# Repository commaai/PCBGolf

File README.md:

<div align="center">
<h1>PCBGolf Challenge</h1>
<h3>How small can you make this PCBA?</h3>
<h3>
  <a href="https://comma.ai/leaderboard#pcbgolf_challenge">Leaderboard</a>
  <span> · </span>
  <a href="https://comma.ai/jobs">comma.ai/jobs</a>
  <span> · </span>
  <a href="https://discord.comma.ai">Discord</a>
  <span> · </span>
  <a href="https://x.com/comma_ai">X</a>
</h3>
</div>

## The Board

The schematic is loosely based on [our panda jungle v2](https://www.comma.ai/shop/panda-jungle), a development and debugging board for comma devices and pandas. This version includes:

* 12V DC input with onboard 5V and 3.3V supplies
* Four [OBD-C](https://github.com/commaai/hardware/blob/master/harness/OBD-C.sch.pdf) device ports with individually controlled power and current monitoring
* Four CAN-FD transceivers and ignition simulation circuitry
* A USB hub and USB-C host connection
* A microcontroller and microSD card slot
* A push button and status LEDs

Explore in your browser with KiCanvas: [PCB layout](https://kicanvas.org/?github=https%3A%2F%2Fgithub.com%2Fcommaai%2FPCBGolf%2Fblob%2Fmaster%2Fpcbgolf.kicad_pcb).

Schematics: [Power](https://kicanvas.org/?github=https%3A%2F%2Fgithub.com%2Fcommaai%2FPCBGolf%2Fblob%2Fmaster%2Fpcbgolf.kicad_sch) · [Microcontroller](https://kicanvas.org/?github=https%3A%2F%2Fgithub.com%2Fcommaai%2FPCBGolf%2Fblob%2Fmaster%2Fpcbgolf_2.kicad_sch) · [USB & microSD](https://kicanvas.org/?github=https%3A%2F%2Fgithub.com%2Fcommaai%2FPCBGolf%2Fblob%2Fmaster%2Fpcbgolf_3.kicad_sch) · [CAN](https://kicanvas.org/?github=https%3A%2F%2Fgithub.com%2Fcommaai%2FPCBGolf%2Fblob%2Fmaster%2Fpcbgolf_4.kicad_sch) · [OBD-C ports](https://kicanvas.org/?github=https%3A%2F%2Fgithub.com%2Fcommaai%2FPCBGolf%2Fblob%2Fmaster%2Fpcbgolf_5.kicad_sch)

## The Challenge

Your goal is to make the most compact, efficient PCBA that retains the same interfaces and functionality as the original design. The lowest score wins.

<p align="center">
  <picture>
    <source media="(prefers-color-scheme: dark)" srcset="./assets/score-dark.svg">
    
  </picture>
</p>

### Rules

* The bare PCB(s) must be fully manufacturable by JLCPCB.
* It must be possible to actually assemble the PCBA.
* The assembled product must work and be usable.
* Mating connectors must remain mechanically and electrically compatible.
* Optimizations that require firmware changes are allowed.

### Prize

Lowest score on the [leaderboard](https://comma.ai/leaderboard#pcbgolf_challenge) by **October 12, 2026** wins **$1,000 cash**.

## Submission

Submit a `.zip` file containing your finalized KiCad project and a STEP file of the final assembly [here](https://forms.gle/US88Hg7UR6bBuW3BA).
Competitive scores will be posted on the [leaderboard](https://comma.ai/leaderboard#pcbgolf_challenge) after review. Multiple submissions allowed.

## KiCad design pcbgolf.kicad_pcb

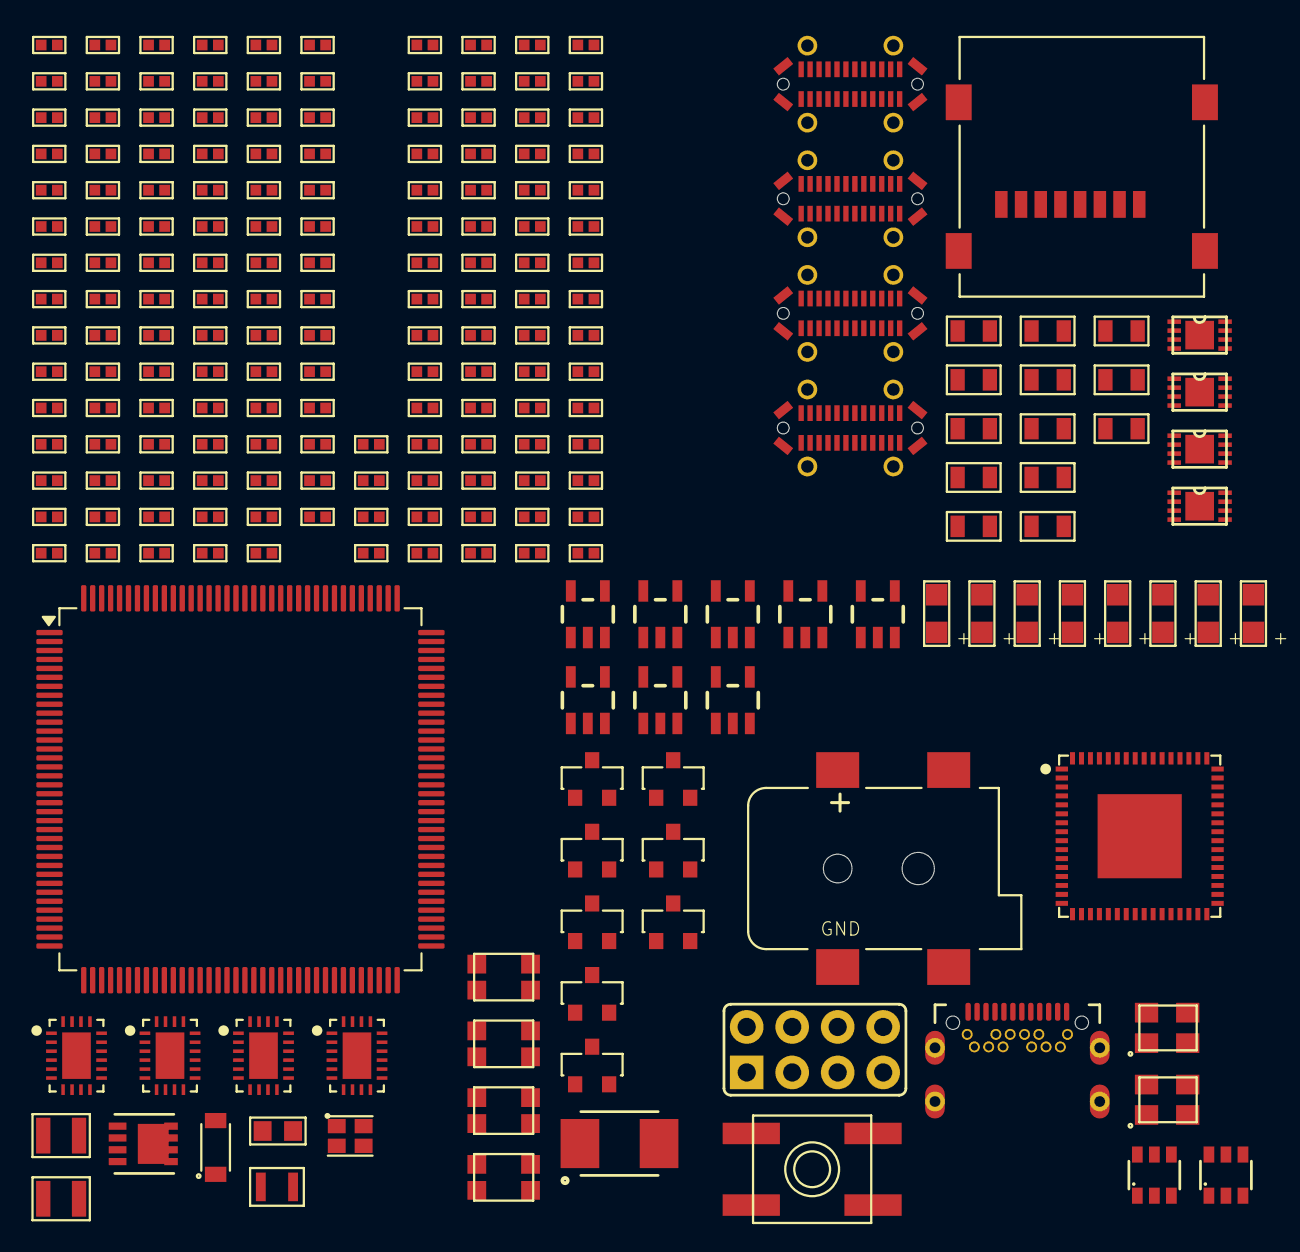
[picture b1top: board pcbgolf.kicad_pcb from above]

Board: 4 copper layers, 225 parts (0 on the bottom side), 183 nets, no tracks yet.

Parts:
C1, C3, C8, C12, C13, C15, C19, C20, C21: 10uF; 0805-C
C2, C4, C5, C7, C9, C11, C16, C18, C22, C23, C24, C26, C27, C30, C31, C35, C36, C38, C39, C40, C41, C42, C43, C44, C45, C46, C47, C48, C49: 100nF; 0402-C
C6, C10: DNP; 0402-C
C14, C17, C28, C32: 12pF; 0402-C
C25: 220pF; 0402-C
C29, C33, C34, C37: 10u; 0402-C
C50, C51, C52, C53: 10u; 0805-C
D1: TVS-BI-DO214AA; DO-214AA(SMB)
D2: DIODEDB2W40100L; SOD-123F
J1: DCBARRELSMT; DCJACK_2MM_SMT
J2: MICRO_SD-0472192001; 0472192001
J3: USB-C-FEMALE; DX07S024XJ1R1100
J4: CAN; 2X04
J5, J6, J7, J8: USB-C-FEMALEGCT; USB-C-FEMALE-VERT-GCT
L1, L2: 3u3; L-1008
L3: L-US-L2; 0603-L
L4: 2u2; 0806
L5, L6, L7, L8: ACT1210D_CHOKE; CHOKE-3.2X2.5
LED1: CREE-RGB-CLMVC
LED2: CAN0; CHIPLED
LED3: CAN1; CHIPLED
LED4: CAN2; CHIPLED
LED5: CAN3; CHIPLED
LED6, LED7, LED8, LED9: CH1_PWR; CHIPLED
LED10, LED11, LED12, LED13, LED14, LED15, LED16, LED17: LED-CC-GREEN-RED-AM23ESG; SOT23-3
Q1: SIS427-VI; PP-1212-8
Q2, Q3, Q4, Q5, Q6, Q7, Q8, Q9: NFET-DUAL-COMMON-SOURCE-QS5K2; SOT23-5
R1, R3, R7, R8, R9, R11, R12, R28, R29, R30, R31, R32, R33, R34, R35, R36, R37, R44, R45, R78, R79, R80, R81, R98, R99, R100, R101, R102, R103, R104, R105, R122, R123, R124, R125: 10k; 0402-R
R2, R21, R23, R90, R92, R94, R96, R114, R116, R118, R120: 1k; 0402-R
R4, R5, R6, R13, R14, R15, R16, R17, R18, R19, R20, R24, R25: 100k; 0402-R
R10: 52k3; 0402-R
R22: 2k7; 0402-R
R26: 1M; 0402-R
R27: 12k; 0402-R
R38, R39, R40, R41, R42, R43: 0R; 0402-R
R46, R47, R48, R49: 60; 0402-R
R62, R63, R64, R65: 330; 0402-R
R66, R67, R68, R69: 28k; 0402-R
R70, R71, R72, R73: 33k; 0402-R
R74, R75, R76, R77: 3k3; 0402-R
R82, R83, R84, R85, R86, R87, R88, R89, R91, R93, R95, R97, R106, R107, R108, R109, R110, R111, R112, R113, R115, R117, R119, R121: 100; 0402-R
SW1: SPST-2-4PIN; EVQ-Q2
U1, U2: AP62300T; SOT23-6
U3: STM32H725ZGTx; LQFP-144_20x20mm_P0.5mm
U4: USB2517; QFN64-9X9
U5, U6, U7, U8: MCP2542FDT-E/MNY; TDFN8_2X3MC_MCH
U13, U14, U15, U16: TPS25942; WQFN20
Y1: 25MHz; XTAL-3.2X2.5
Y2: 24MHz; XTAL-3.2X2.5

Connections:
+3V3: C6.2, C7.1, C8.1, C19.1, C20.1, C23.1, C24.1, C26.1, C27.1, C30.2, C31.2, C37.1, C42.1, C43.1, C44.1, C45.1, J2.4 (VDD), L1.2, L3.1, LED1.U1 (COM+), R4.1, R5.1, R6.1, R11.1, R28.1, R29.1, R30.1, R33.1, R34.1, R35.1, R36.1, R37.1, SW1.B (S), SW1.B' (S1), U3.7 (VDD), U3.8 (VBAT), U3.13 (VDD), U3.16 (VDDSMPS), U3.19 (VDD), U3.32 (VDD), U3.42 (VDD), U3.56 (VDD), U3.71 (VDD), U3.79 (VDD), U3.90 (VDD50USB), U3.91 (VDD33USB), U3.92 (VDD), U3.106 (VDD), U3.119 (VDD), U3.129 (VDD), U3.144 (VDD), U4.5 (VDDA33), U4.10 (VDDA33), U4.13 (CFG_SEL2), U4.24 (VDD33CR), U4.42 (CFG_SEL1), U4.43 (RESET_N), U4.46 (VDD33), U4.52 (VDDA33), U4.57 (VDDA33), U4.64 (VDD33PLL), U5.5 (VIO), U6.5 (VIO), U7.5 (VIO), U8.5 (VIO)
+5V: C1.1, C2.1, C10.2, C11.1, C12.1, C13.1, C38.1, C39.1, C40.1, C41.1, L2.2, R1.1, R10.2, U1.3 (IN), U5.3 (VDD), U6.3 (VDD), U7.3 (VDD), U8.3 (VDD)
+12V: C3.1, C5.1, C46.1, C47.1, C48.1, C49.1, C50.1, C51.1, C52.1, C53.1, D2.1 (C), Q1.1 (S), Q1.2 (S), Q1.3 (S), R7.1, U2.3 (IN), U13.9 (VIN), U13.10 (VIN), U13.11 (VIN), U13.12 (VIN), U13.13 (VIN), U14.9 (VIN), U14.10 (VIN), U14.11 (VIN), U14.12 (VIN), U14.13 (VIN), U15.9 (VIN), U15.10 (VIN), U15.11 (VIN), U15.12 (VIN), U15.13 (VIN), U16.9 (VIN), U16.10 (VIN), U16.11 (VIN), U16.12 (VIN), U16.13 (VIN)
BTN: R12.2, SW1.A, SW1.A' (P1), U3.65 (PE15), U3.135 (BOOT0)
CAN0_EN: U3.134 (PB7), U5.8 (STBY)
CAN0_H: J4.2, J5.A2 (TX1+), J6.A2 (TX1+), J7.A2 (TX1+), J8.A2 (TX1+), L5.4, R46.2
CAN0_L: J4.1, J5.A3 (TX1-), J6.A3 (TX1-), J7.A3 (TX1-), J8.A3 (TX1-), L5.3, R46.1
CAN0_RX: U3.136 (PB8), U5.4 (RXD)
CAN0_TX: U3.137 (PB9), U5.1 (TXD)
CAN1_EN: U3.130 (PB3(JTDO), U6.8 (STBY)
CAN1_H: J4.4, J5.A11 (RX2+), J6.A11 (RX2+), J7.A11 (RX2+), J8.A11 (RX2+), L6.4, R47.2
CAN1_L: J4.3, J5.A10 (RX2-), J6.A10 (RX2-), J7.A10 (RX2-), J8.A10 (RX2-), L6.3, R47.1
CAN1_RX: U3.132 (PB5), U6.4 (RXD)
CAN1_TX: U3.133 (PB6), U6.1 (TXD)
CAN2_EN: U3.121 (PD7), U7.8 (STBY)
CAN2_H: J4.6, J5.B2 (TX2+), J6.B2 (TX2+), J7.B2 (TX2+), J8.B2 (TX2+), L7.4, R48.2
CAN2_L: J4.5, J5.B3 (TX2-), J6.B3 (TX2-), J7.B3 (TX2-), J8.B3 (TX2-), L7.3, R48.1
CAN2_RX: U3.123 (PG10), U7.4 (RXD)
CAN2_TX: U3.122 (PG9), U7.1 (TXD)
CAN3_EN: U3.131 (PB4(NJTRST)), U8.8 (STBY)
CAN3_H: J4.8, J5.B11 (RX1+), J6.B11 (RX1+), J7.B11 (RX1+), J8.B11 (RX1+), L8.4, R49.2
CAN3_L: J4.7, J5.B10 (RX1-), J6.B10 (RX1-), J7.B10 (RX1-), J8.B10 (RX1-), L8.3, R49.1
CAN3_RX: U3.72 (PB12), U8.4 (RXD)
CAN3_TX: U3.73 (PB13), U8.1 (TXD)
CH1_D_N: J5.A7 (D-A), J5.B7 (D-B), U4.1 (USBDN1_DM)
CH1_D_P: J5.A6 (D+A), J5.B6 (D+B), U4.2 (USBDN1_DP)
CH1_IMON: R70.2, U3.47 (PC4), U13.19 (IMON)
CH1_PWR_EN: U3.37 (PA0), U13.14 (EN)
CH1_SBU1: J5.A8 (SBU1), R19.2, R90.2, R91.2
CH1_SBU1_IGN: Q2.1 (G1), R78.1, R83.2, U3.112 (PD0)
CH1_SBU1_RELAY: Q2.3 (G2), R82.2, R98.2, U3.113 (PD1)
CH1_SBU2: J5.B8 (SBU2), R20.2, R114.2, R115.2
CH1_SBU2_IGN: Q6.1 (G1), R102.1, R107.2, U3.115 (PD3)
CH1_SBU2_RELAY: Q6.3 (G2), R106.2, R122.2, U3.116 (PD4)
CH2_D_N: J6.A7 (D-A), J6.B7 (D-B), U4.3 (USBDN2_DM)
CH2_D_P: J6.A6 (D+A), J6.B6 (D+B), U4.4 (USBDN2_DP)
CH2_IMON: R71.2, U3.50 (PB1), U14.19 (IMON)
CH2_PWR_EN: U3.38 (PA1), U14.14 (EN)
CH2_SBU1: J6.A8 (SBU1), R15.2, R92.2, R93.2
CH2_SBU1_IGN: Q3.1 (G1), R79.1, R85.2, U3.117 (PD5)
CH2_SBU1_RELAY: Q3.3 (G2), R84.2, R99.2, U3.120 (PD6)
CH2_SBU2: J6.B8 (SBU2), R13.2, R116.2, R117.2
CH2_SBU2_IGN: Q7.1 (G1), R103.1, R109.2, U3.76 (PD8)
CH2_SBU2_RELAY: Q7.3 (G2), R108.2, R123.2, U3.78 (PD10)
CH3_D_N: J7.A7 (D-A), J7.B7 (D-B), U4.6 (USBDN3_DM)
CH3_D_P: J7.A6 (D+A), J7.B6 (D+B), U4.7 (USBDN3_DP)
CH3_IMON: R72.2, U3.52 (PF11), U15.19 (IMON)
CH3_PWR_EN: U3.43 (PA4), U15.14 (EN)
CH3_SBU1: J7.A8 (SBU1), R17.2, R94.2, R95.2
CH3_SBU1_IGN: Q4.1 (G1), R80.1, R87.2, U3.82 (PD12)
CH3_SBU1_RELAY: Q4.3 (G2), R86.2, R100.2, U3.81 (PD11)
CH3_SBU2: J7.B8 (SBU2), R18.2, R118.2, R119.2
CH3_SBU2_IGN: Q8.1 (G1), R104.1, R111.2, U3.77 (PD9)
CH3_SBU2_RELAY: Q8.3 (G2), R110.2, R124.2, U3.83 (PD13)
CH4_D_N: J8.A7 (D-A), J8.B7 (D-B), U4.8 (USBDN4_DM)
CH4_D_P: J8.A6 (D+A), J8.B6 (D+B), U4.9 (USBDN4_DP)
CH4_IMON: R73.2, U3.45 (PA6), U16.19 (IMON)
CH4_PWR_EN: U3.44 (PA5), U16.14 (EN)
CH4_SBU1: J8.A8 (SBU1), R16.2, R96.2, R97.2
CH4_SBU1_IGN: Q5.1 (G1), R81.1, R89.2, U3.84 (PD14)
CH4_SBU1_RELAY: Q5.3 (G2), R88.2, R101.2, U3.85 (PD15)
CH4_SBU2: J8.B8 (SBU2), R14.2, R120.2, R121.2
CH4_SBU2_IGN: Q9.1 (G1), R105.1, R113.2, U3.138 (PE0)
CH4_SBU2_RELAY: Q9.3 (G2), R112.2, R125.2, U3.139 (PE1)
GND: C1.2, C2.2, C3.2, C5.2, C7.2, C8.2, C11.2, C12.2, C13.2, C14.2, C15.2, C16.2, C17.2, C18.2, C19.2, C20.2, C21.2, C22.2, C23.2, C24.2, C25.2, C26.2, C27.2, C28.2, C29.2, C30.1, C31.1, C32.2, C33.2, C34.2, C35.1, C36.1, C37.2, C38.2, C39.2, C40.2, C41.2, C42.2, C43.2, C44.2, C45.2, C46.2, C47.2, C48.2, C49.2, C50.2, C51.2, C52.2, C53.2, D1.1, J1.GND (GNDBREAK), J1.GNDBREAK (GND), J2.6 (VSS), J2.G1 (GND), J2.G2 (GND), J2.G3 (GND), J2.G4 (GND), J3.A1 (GND), J3.A12 (GND), J3.B1 (GND), J3.B1T (GND), J3.B12 (GND), J3.B12T (GND), J3.S1B (SHIELDA), J3.S1T (SHIELDA), J3.S1TH (SHIELDA), J3.S2B (SHIELDA), J3.S2T (SHIELDA), J3.S2TH (SHIELDA), J3.S3B (SHIELDB), J3.S3T (SHIELDB), J3.S3TH (SHIELDB), J3.S4B (SHIELDB), J3.S4T (SHIELDB), J3.S4TH (SHIELDB), J5.A1 (GND), J5.A12 (GND), J5.B1 (GND), J5.B12 (GND), J5.S1 (SHIELDA), J5.S2 (SHIELDA), J5.S3 (SHIELDA), J5.S4 (SHIELDA), J5.S11 (SHIELDB), J5.S12 (SHIELDB), J5.S13 (SHIELDB), J5.S14 (SHIELDB), J6.A1 (GND), J6.A12 (GND), J6.B1 (GND), J6.B12 (GND), J6.S1 (SHIELDA), J6.S2 (SHIELDA), J6.S3 (SHIELDA), J6.S4 (SHIELDA), J6.S11 (SHIELDB), J6.S12 (SHIELDB), J6.S13 (SHIELDB), J6.S14 (SHIELDB), J7.A1 (GND), J7.A12 (GND), J7.B1 (GND), J7.B12 (GND), J7.S1 (SHIELDA), J7.S2 (SHIELDA), J7.S3 (SHIELDA), J7.S4 (SHIELDA), J7.S11 (SHIELDB), J7.S12 (SHIELDB), J7.S13 (SHIELDB), J7.S14 (SHIELDB), J8.A1 (GND), J8.A12 (GND), J8.B1 (GND), J8.B12 (GND), J8.S1 (SHIELDA), J8.S2 (SHIELDA), J8.S3 (SHIELDA), J8.S4 (SHIELDA), J8.S11 (SHIELDB), J8.S12 (SHIELDB), J8.S13 (SHIELDB), J8.S14 (SHIELDB), LED2.C, LED3.C, LED4.C, LED5.C, LED6.C, LED7.C, LED8.C, LED9.C, LED10.3 (C), LED11.3 (C), LED12.3 (C), LED13.3 (C), LED14.3 (C), LED15.3 (C), LED16.3 (C), LED17.3 (C), Q2.2 (S), Q3.2 (S), Q4.2 (S), Q5.2 (S), Q6.2 (S), Q7.2 (S), Q8.2 (S), Q9.2 (S), R2.1, R3.2, R8.2, R9.2, R12.1, R25.1, R27.1, R31.2, R32.2, R44.2, R45.2, R66.1, R67.1, R68.1, R69.1, R70.1, R71.1, R72.1, R73.1, R78.2, R79.2, R80.2, R81.2, R98.1, R99.1, R100.1, R101.1, R102.2, R103.2, R104.2, R105.2, R122.1, R123.1, R124.1, R125.1, U1.1 (GND), U2.1 (GND), U3.6 (VSS), U3.12 (VSS), U3.14 (VSSSMPS), U3.18 (VSS), U3.33 (VSS), U3.34 (VSSA), U3.41 (VSS), U3.55 (VSS), U3.69 (VSS), U3.80 (VSS), U3.89 (VSS), U3.104 (VSS), U3.118 (VSS), U3.128 (VSS), U3.141 (VSS), U4.19 (TEST), U4.PAD (VSS), U5.2 (VSS), U5.PAD (EPAD), U6.2 (VSS), U6.PAD (EPAD), U7.2 (VSS), U7.PAD (EPAD), U8.2 (VSS), U8.PAD (EPAD), U13.3 (PGTH), U13.15 (OVP), U13.16 (GND), U13.PAD (GND), U14.3 (PGTH), U14.15 (OVP), U14.16 (GND), U14.PAD (GND), U15.3 (PGTH), U15.15 (OVP), U15.16 (GND), U15.PAD (GND), U16.3 (PGTH), U16.15 (OVP), U16.16 (GND), U16.PAD (GND), Y1.2 (3), Y1.4 (3), Y2.2 (3), Y2.4 (3)
HUB_SCL: R30.2, U3.66 (PB10), U4.41 (SCL)
HUB_SDA: R28.2, U3.67 (PB11), U4.40 (SDA)
LED_B: R23.2, U3.1 (PE2)
LED_CAN0: R62.1, U3.57 (PE7)
LED_CAN1: R63.1, U3.58 (PE8)
LED_CAN2: R64.1, U3.59 (PE9)
LED_CAN3: R65.1, U3.60 (PE10)
LED_G: R22.2, U3.2 (PE3)
LED_R: R21.2, U3.3 (PE4)
unnamed: D2.2 (A), Q1.4 (G), R2.2
unnamed: D1.2, J1.PWR1 (PWR), Q1.5 (D), Q1.6 (D), Q1.7 (D), Q1.8 (D), Q1.9 (D)
unnamed: J2.2 (CD/DAT3), R36.2, R41.2
unnamed: J2.5 (CLK), R43.2
unnamed: J2.3 (CMD), R37.2, R42.2
unnamed: J2.7 (DAT0), R33.2, R38.2
unnamed: J2.8 (DAT1), R34.2, R39.2
unnamed: J2.1 (DAT2), R35.2, R40.2
unnamed: J3.A5 (CC1), R31.1, R32.1
unnamed: J3.B5 (CC2), J3.B5T (CC2), R44.1, R45.1
unnamed: J5.A4 (VBUS), J5.A9 (VBUS), J5.B4 (VBUS), J5.B9 (VBUS), R74.1, U13.4 (VOUT), U13.5 (VOUT), U13.6 (VOUT), U13.7 (VOUT), U13.8 (VOUT)
unnamed: J6.A4 (VBUS), J6.A9 (VBUS), J6.B4 (VBUS), J6.B9 (VBUS), R75.1, U14.4 (VOUT), U14.5 (VOUT), U14.6 (VOUT), U14.7 (VOUT), U14.8 (VOUT)
unnamed: J7.A4 (VBUS), J7.A9 (VBUS), J7.B4 (VBUS), J7.B9 (VBUS), R76.1, U15.4 (VOUT), U15.5 (VOUT), U15.6 (VOUT), U15.7 (VOUT), U15.8 (VOUT)
unnamed: J8.A4 (VBUS), J8.A9 (VBUS), J8.B4 (VBUS), J8.B9 (VBUS), R77.1, U16.4 (VOUT), U16.5 (VOUT), U16.6 (VOUT), U16.7 (VOUT), U16.8 (VOUT)
unnamed: LED1.U4 (B-), R23.1
unnamed: LED1.U3 (G-), R22.1
unnamed: LED1.U2 (R-), R21.1
unnamed: LED2.A, R62.2
unnamed: LED3.A, R63.2
unnamed: LED4.A, R64.2
unnamed: LED5.A, R65.2
unnamed: LED6.A, R74.2
unnamed: LED7.A, R75.2
unnamed: LED8.A, R76.2
unnamed: LED9.A, R77.2
unnamed: LED10.2 (AG), R82.1
unnamed: LED10.1 (AR), R83.1
unnamed: LED11.2 (AG), R84.1
unnamed: LED11.1 (AR), R85.1
unnamed: LED12.2 (AG), R86.1
unnamed: LED12.1 (AR), R87.1
unnamed: LED13.2 (AG), R88.1
unnamed: LED13.1 (AR), R89.1
unnamed: LED14.2 (AG), R106.1
unnamed: LED14.1 (AR), R107.1
unnamed: LED15.2 (AG), R108.1
unnamed: LED15.1 (AR), R109.1
unnamed: LED16.2 (AG), R110.1
unnamed: LED16.1 (AR), R111.1
unnamed: LED17.2 (AG), R112.1
unnamed: LED17.1 (AR), R113.1
unnamed: Q2.5 (D1), R90.1
unnamed: Q2.4 (D2), R91.1
unnamed: Q3.5 (D1), R92.1
unnamed: Q3.4 (D2), R93.1
unnamed: Q4.5 (D1), R94.1
unnamed: Q4.4 (D2), R95.1
unnamed: Q5.5 (D1), R96.1
unnamed: Q5.4 (D2), R97.1
unnamed: Q6.5 (D1), R114.1
unnamed: Q6.4 (D2), R115.1
unnamed: Q7.5 (D1), R116.1
unnamed: Q7.4 (D2), R117.1
unnamed: Q8.5 (D1), R118.1
unnamed: Q8.4 (D2), R119.1
unnamed: Q9.5 (D1), R120.1
unnamed: Q9.4 (D2), R121.1
unnamed: C4.1, U1.6 (BST)
unnamed: R1.2, U1.5 (EN)
unnamed: C6.1, R3.1, R4.2, R5.2, R6.2, U1.4 (FB)
unnamed: C4.2, L1.1, U1.2 (SW)
unnamed: C9.1, U2.6 (BST)
unnamed: R7.2, R8.1, U2.5 (EN)
unnamed: C10.1, R9.1, R10.1, U2.4 (FB)
unnamed: C9.2, L2.1, U2.2 (SW)
unnamed: R17.1, U3.28 (PC0)
unnamed: R18.1, U3.29 (PC1)
unnamed: R19.1, U3.30 (PC2_C)
unnamed: R20.1, U3.31 (PC3_C)
unnamed: R11.2, U3.142 (PDR_ON)
unnamed: R13.1, U3.21 (PF7)
unnamed: R14.1, U3.22 (PF8)
unnamed: R15.1, U3.23 (PF9)
unnamed: R16.1, U3.24 (PF10)
unnamed: C14.1, U3.25 (PH0), Y1.1
unnamed: C17.1, U3.26 (PH1), Y1.3 (2)
unnamed: R27.2, U4.63 (RBIAS)
unnamed: R29.2, U4.45 (SUSP_IND)
unnamed: R24.1, R25.2, U4.44 (VBUS_DET)
unnamed: C33.1, C35.2, U4.25 (VDD18)
unnamed: C34.1, C36.2, U4.62 (VDD18PLL)
unnamed: C28.1, R26.2, U4.61 (XTAL1), Y2.1
unnamed: C32.1, R26.1, U4.60 (XTAL2), Y2.3 (2)
unnamed: L5.1, U5.7 (CANH)
unnamed: L5.2, U5.6 (CANL)
unnamed: L6.1, U6.7 (CANH)
unnamed: L6.2, U6.6 (CANL)
unnamed: L7.1, U7.7 (CANH)
unnamed: L7.2, U7.6 (CANL)
unnamed: L8.1, U8.7 (CANH)
unnamed: L8.2, U8.6 (CANL)
unnamed: R66.2, U13.17 (ILIM)
unnamed: R67.2, U14.17 (ILIM)
unnamed: R68.2, U15.17 (ILIM)
unnamed: R69.2, U16.17 (ILIM)
SD_CLK: R43.1, U3.111 (PC12)
SD_CMD: R42.1, U3.114 (PD2)
SD_D0: R38.1, U3.95 (PC8)
SD_D1: R39.1, U3.96 (PC9)
SD_D2: R40.1, U3.109 (PC10)
SD_D3: R41.1, U3.110 (PC11)
STM_D_N: U3.100 (PA11), U4.55 (USBDN7_DM)
STM_D_P: U3.101 (PA12), U4.56 (USBDN7_DP)
USB_D_N: J3.A7 (D-A), J3.B7 (D-B), J3.B7T (D-B), U4.58 (USBUP_DM)
USB_D_P: J3.A6 (D+A), J3.B6 (D+B), J3.B6T (D+B), U4.59 (USBUP_DP)
VBUS: C29.1, J3.A4 (VBUS), J3.A9 (VBUS), J3.B4 (VBUS), J3.B4T (VBUS), J3.B9 (VBUS), J3.B9T (VBUS), R24.2
VDDA: C22.1, L3.2, U3.35 (VREF+), U3.36 (VDDA)
VDDLDO: C15.1, C16.1, C18.1, C21.1, L4.1, U3.17 (VFBSMPS), U3.68 (VCAP), U3.70 (VDDLDO), U3.103 (VCAP), U3.105 (VDDLDO), U3.140 (VCAP), U3.143 (VDDLDO)
VLXSMPS: C25.1, L4.2, U3.15 (VLXSMPS)

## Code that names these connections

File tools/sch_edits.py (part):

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LED_NET_ANCHOR = (222.25, 31.75)  # freed end of the U9->R62 wire, cluster 0

MCU_REF = "U3"
LED_PINS = ["PE7", "PE8", "PE9", "PE10"]
LED_NETS = [f"LED_CAN{k}" for k in range(4)]

BH_BOX = ((198.0, 226.0), (105.0, 124.0))   # BH1-4, their GNDs, their wires
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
